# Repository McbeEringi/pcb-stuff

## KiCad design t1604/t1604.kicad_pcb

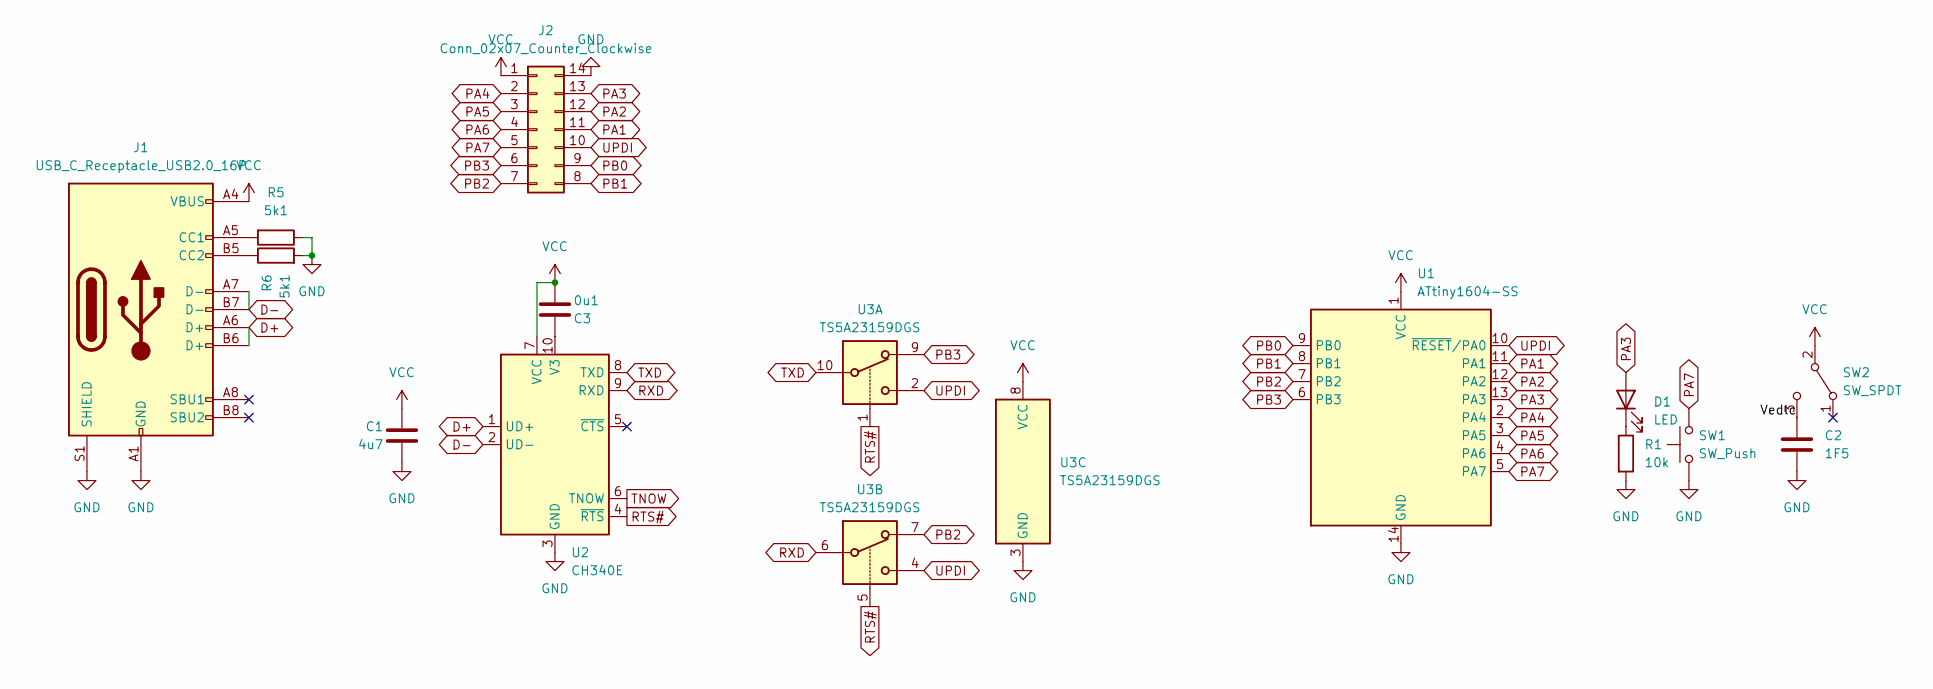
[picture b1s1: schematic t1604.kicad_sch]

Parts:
C1: 4u7; C_0603_1608Metric
C2: 1F5; edlc
C3: 0u1; C_0603_1608Metric
D1: LED; LED_0603_1608Metric
J1: USB_C_Receptacle_USB2.0_16P; USB_C_Receptacle_GCT_USB4105-xx-A_16P_TopMnt_Horizontal
J2: Conn_02x07_Counter_Clockwise; DIP-14_W10.16mm
R1: 10k; R_0603_1608Metric
R5, R6: 5k1; R_0603_1608Metric
SW1: SW_Push; alps-skrp
SW2: SW_SPDT; sw
U1: ATtiny1604-SS; SOIC-14_3.9x8.7mm_P1.27mm
U2: CH340E; MSOP-10_3x3mm_P0.5mm
U3: TS5A23159DGS; VSSOP-10_3x3mm_P0.5mm

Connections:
/Vedlc: C2.1, SW2.3 (C)
D+: J1.A6 (D+), J1.B6 (D+), U2.1 (UD+)
D-: J1.A7 (D-), J1.B7 (D-), U2.2 (UD-)
GND: C1.2, C2.2, J1.A1 (GND), J1.A12 (GND), J1.B1 (GND), J1.B12 (GND), J1.S1 (SHIELD), J2.14, R1.2, R5.1, R6.2, SW1.1, U1.14 (GND), U2.3 (GND), U3.3 (GND)
unnamed: D1.1 (K), R1.1
unnamed: J1.A5 (CC1), R5.2
unnamed: J1.B5 (CC2), R6.1
unnamed: C3.1, U2.10 (V3)
PA1: J2.11, U1.11 (PA1)
PA2: J2.12, U1.12 (PA2)
PA3: D1.2 (A), J2.13, U1.13 (PA3)
PA4: J2.2, U1.2 (PA4)
PA5: J2.3, U1.3 (PA5)
PA6: J2.4, U1.4 (PA6)
PA7: J2.5, SW1.2, U1.5 (PA7)
PB0: J2.9, U1.9 (PB0)
PB1: J2.8, U1.8 (PB1)
PB2: J2.7, U1.7 (PB2), U3.7
PB3: J2.6, U1.6 (PB3), U3.9
RTS#: U2.4 (~RTS), U3.1, U3.5
RXD: U2.9 (RXD), U3.6
TNOW: U2.6 (TNOW)
TXD: U2.8 (TXD), U3.10
UPDI: J2.10, U1.10 (~RESET/PA0), U3.2, U3.4
VCC: C1.1, C3.2, J1.A4 (VBUS), J1.A9 (VBUS), J1.B4 (VBUS), J1.B9 (VBUS), J2.1, SW2.2 (B), U1.1 (VCC), U2.7 (VCC), U3.8 (VCC)

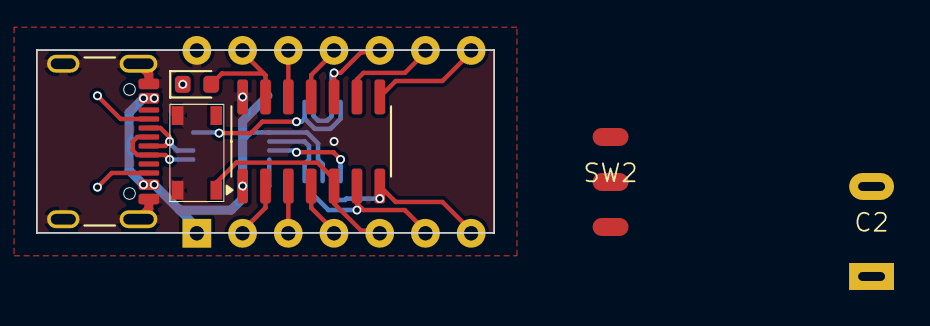
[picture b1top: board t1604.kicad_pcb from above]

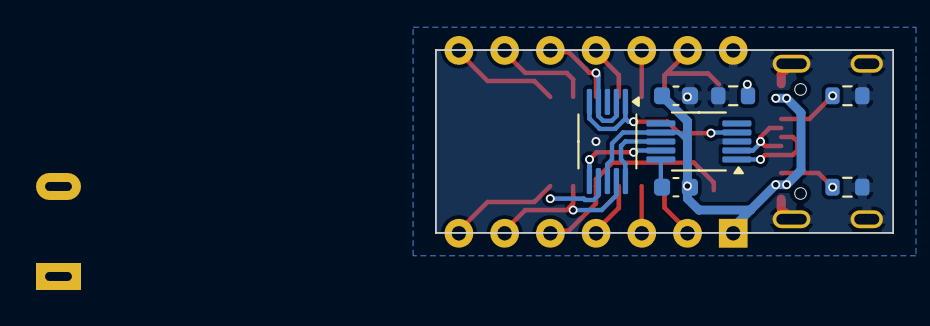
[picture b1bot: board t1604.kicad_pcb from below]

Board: 2 copper layers, 25.4 x 10.2 mm, 14 parts (7 on the bottom side), 24 nets.

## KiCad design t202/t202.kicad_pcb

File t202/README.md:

# 8pin tinyAVR開発ボード

## 機能

- serialupdi書き込み機内蔵
- ELDC搭載で電源無しで駆動

## 部品

- [ATTiny202](https://akizukidenshi.com/catalog/g/gI-15731/)
- serialupdi
  - [CH340K](https://akizukidenshi.com/catalog/g/gI-16306/)
  - [1608サイズ 0.1uF](https://akizukidenshi.com/catalog/g/gP-13374/) *2
- LED
  - 1608サイズ LED
  - 1608サイズ LED電流制限抵抗(10kとか)
- スイッチ
  - [表面実装タクトスイッチ](https://akizukidenshi.com/catalog/g/gP-14888/)
- EDLC
  - [縦型EDLC 1.5F](https://akizukidenshi.com/catalog/g/gP-04300/)
  - [スライドスイッチ](https://akizukidenshi.com/catalog/g/gP-15707/)

## 組み立て&使い方

表にch340k裏にattiny202
シルクが長いところに凹みを合わせる

裏面の部品配置

```text
 |USB|

  avr

| | ->|-
= ξ
| | -||-
```

LED@PB3
SW@PB7

`avrdude -p t202 -c serialupdi`

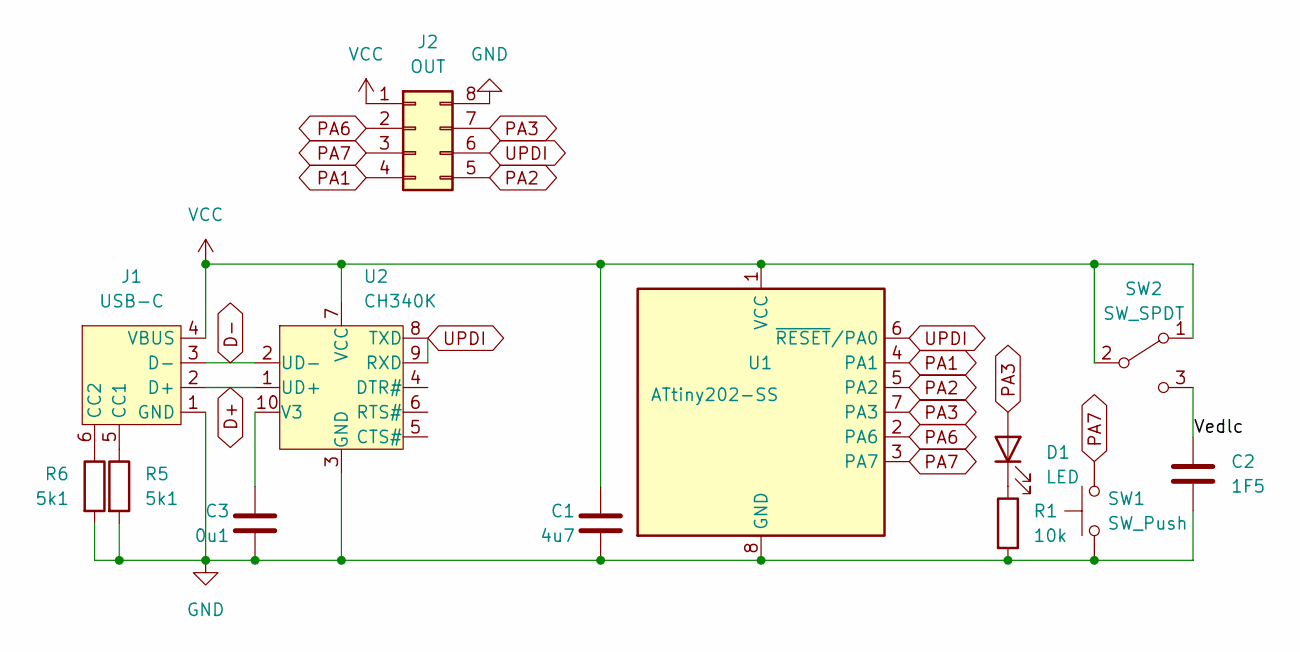
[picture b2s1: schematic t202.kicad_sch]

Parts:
C1: 4u7; C_0603_1608Metric
C2: 1F5; edlc
C3: 0u1; C_0603_1608Metric
D1: LED; LED_0603_1608Metric
J1: USB-C
J2: OUT; DIP-8_W7.62mm_Socket
R1: 10k; R_0603_1608Metric
R5, R6: 5k1; R_0603_1608Metric
SW1: SW_Push; sw_push_smd
SW2: SW_SPDT; sw
U1: ATtiny202-SS; SOIC-8_3.9x4.9mm_P1.27mm
U2: CH340K; SSOP-10_3.9x4.9mm_P1.00mm

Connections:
/Vedlc: C2.1, SW2.3 (C)
D+: J1.2 (D+), U2.1 (UD+)
D-: J1.3 (D-), U2.2 (UD-)
GND: C1.2, C2.2, C3.2, J1.1 (GND), J2.8, R1.2, R5.2, R6.2, SW1.1, U1.8 (GND), U2.3 (GND)
unnamed: D1.1 (K), R1.1
unnamed: J1.5 (CC1), R5.1
unnamed: J1.6 (CC2), R6.1
unnamed: C3.1, U2.10 (V3)
PA1: J2.4, U1.4 (PA1)
PA2: J2.5, U1.5 (PA2)
PA3: D1.2 (A), J2.7, U1.7 (PA3)
PA6: J2.2, U1.2 (PA6)
PA7: J2.3, SW1.2, U1.3 (PA7)
UPDI: J2.6, U1.6 (~RESET/PA0), U2.8 (TXD), U2.9 (RXD)
VCC: C1.1, J1.4 (VBUS), J2.1, SW2.1 (A), SW2.2 (B), U1.1 (VCC), U2.7 (VCC)

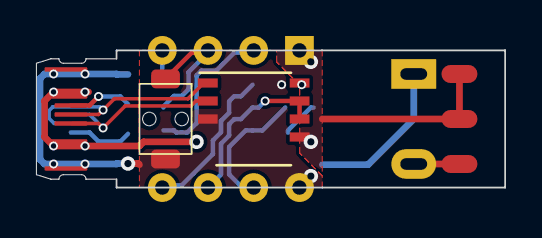
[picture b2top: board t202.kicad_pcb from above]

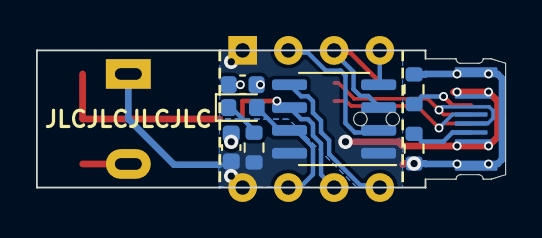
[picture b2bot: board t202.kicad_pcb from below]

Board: 2 copper layers, 26.0 x 7.6 mm, 13 parts (7 on the bottom side), 15 nets.

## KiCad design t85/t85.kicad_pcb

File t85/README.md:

# DigiSpark互換ボード

## 機能

- 超小型8ピンDIPサイズ
- LEDとボタンを搭載
- SMDユニバーサル基板付き

## 部品

- [ATTiny85](https://akizukidenshi.com/catalog/g/gI-09574/)
- バイパスコンデンサ 1608サイズ 大きめに4.7uFとか
- [表面実装タクトスイッチ](https://akizukidenshi.com/catalog/g/gP-14888/)
- LED
  - 1608サイズ LED
  - 1608サイズ LED電流制限抵抗 10kとか
- USB部
  - ダンピング抵抗 1608サイズ 100R(47Rも可) *2
  - プルアップ抵抗 1608サイズ 1.5k
  - [ツェナーダイオード 3.6v SOD323Fパッケージ(UMD2)](https://akizukidenshi.com/catalog/g/gI-07435/) *2

## 組み立て

USB端子の裏側を十分な薄さになるまで削る
表にスイッチとチップ部品

```text
 | USB |
   S W
     101
-|<- -Z<-
103  101
-||- -Z<-
152
```

裏にattiny85
シルクが長いところに凹みを合わせる

SW@PB0
LED@PB1

## ブートローダーの書き込み

<https://github.com/micronucleus/micronucleus>をビルド
windowsはドライバをインストール
ファームウェアをISP書き込み機を用いてを書き込む

参考
<https://qiita.com/nak435/items/67aca33ca49b6f328faa>

## 作例

4和音電子オルゴール <https://github.com/McbeEringi/avr-musicbox>

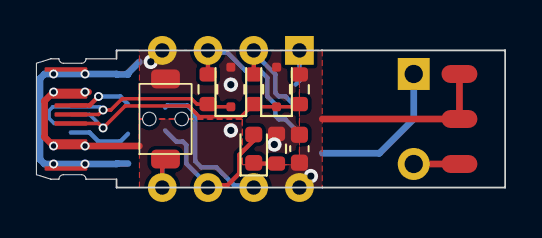
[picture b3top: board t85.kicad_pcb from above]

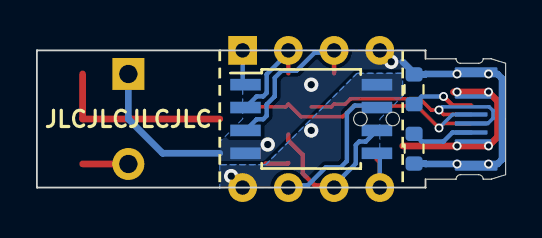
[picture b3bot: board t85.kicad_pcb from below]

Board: 2 copper layers, 26.0 x 7.6 mm, 16 parts (3 on the bottom side), 14 nets.

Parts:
C1: 4u7; C_0603_1608Metric
C2: 1F5; edlc
D1: LED; LED_0603_1608Metric
D2, D3: 3.6; D_SOD-323F
J1: USB-C
J2: OUT; DIP-8_W7.62mm_Socket
R1: 10k; R_0603_1608Metric
R2, R3: 100; R_0603_1608Metric
R4: 1k5; R_0603_1608Metric
R5, R6: 5k1; R_0603_1608Metric
SW1: SW_Push; sw_push_smd
SW2: SW_SPDT; sw
U1: ATtiny85-20S; SOIC-8W_5.3x5.3mm_P1.27mm

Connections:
/Vedlc: C2.1, SW2.3 (C)
D+: D2.1 (K), J1.2 (D+), R3.1
D-: D3.1 (K), J1.3 (D-), R2.2, R4.2
EN: J2.1, U1.1 (~RESET/PB5)
GND: C1.2, C2.2, D2.2 (A), D3.2 (A), J1.1 (GND), J2.4, R1.2, R5.2, R6.2, SW1.1, U1.4 (GND)
unnamed: D1.1 (K), R1.1
unnamed: J1.5 (CC1), R5.1
unnamed: J1.6 (CC2), R6.1
PB0: J2.5, SW1.2, U1.5 (AREF/PB0)
PB1: D1.2 (A), J2.6, U1.6 (PB1)
PB2: J2.7, U1.7 (PB2)
PB3: J2.2, R2.1, U1.2 (XTAL1/PB3)
PB4: J2.3, R3.2, U1.3 (XTAL2/PB4)
VCC: C1.1, J1.4 (VBUS), J2.8, R4.1, SW2.1 (A), SW2.2 (B), U1.8 (VCC)

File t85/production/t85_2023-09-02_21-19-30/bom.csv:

Designator,Footprint,Quantity,Value,LCSC Part #
C1,0603,1,4u7,
D1,0603,1,LED,
"D2, D3",D_SOD-323F,2,3.6,
J1,USB-micro-b,1,USB,
J2,DIP-8_W7.62mm_Socket,1,Conn_02x04_Counter_Clockwise,
R1,0603,1,10k,
"R2, R3",0603,2,100,
R4,0603,1,1k5,
SW1,sw_push_smd,1,SW_Push,
"TP1, TP2",TestPoint_Pad_D1.0mm,2,TestPoint,
U1,SOIC-8W_5.3x5.3mm_P1.27mm,1,ATtiny85-20S,
